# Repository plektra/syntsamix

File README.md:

# Syntsamix

A modular, analog stereo mixer for live electronic music: synthesizers, drum machines and Eurorack modular gear on one desk, with a resonant ladder filter on every channel and a compressor built for bass pumping.

> **Status: in design.** The specification is complete and the schematics for all four prototype boards are done. Nothing has been built yet: no PCB is laid out and the filter breadboard is still waiting for parts. Figures below are design targets, not measurements.

## Goals

- **Made for playing live.** Few controls, each with an obvious musical effect; the mixer is part of the performance, not only a utility.
- **Modular.** Identical stereo channel cards, added one at a time from 1 to 16. No card depends on another, and there is no backplane: cards are joined by multi-drop flat cables in 8-card sections, with the master card at one end.
- **Synth-friendly inputs.** Balanced inputs take everything from consumer line level to hot Eurorack signals of ±12 V peak, with no external attenuator.
- **Analog signal path** with pro headroom: +4 dBu nominal, about +20 dBu internal maximum, +24 dBu at the balanced outputs.
- **Cost-effective.** A tight budget: cheaper parts wherever the audible difference is small.
- **Open design** for anyone to build for themselves (non-commercial license, see below).

## Features

### Channel strip (stereo, every element an L/R pair)

- Balanced 6.3 mm TRS inputs (L/MONO and R) on a separate, swappable passive input module; a mono source in L/MONO feeds both sides
- One wide input trim (about -20 to +20 dB) with **soft clipping**, so overloads saturate gently
- Switchable 100 Hz low-cut
- **24 dB/octave ladder low-pass filter** (Sound Semiconductor SSI2144) with cutoff (20 Hz to 20 kHz), resonance and bypass. Driven "hot" for character, with resonance capped below self-oscillation and the bass loss half compensated
- Cutoff CV input at about 1 V/octave for modulation from modular gear
- 60 mm fader driving a VCA (SSI2162) with a console-style law: +10 dB at the top, 0 dB at 75 % of travel, fully off at the bottom; click-free mute
- Two stereo AUX sends (post-fader, jumper for pre-fader)
- Main or compressor bus assign
- **PFL** (pre-fader listen): headphones switch to the cue bus automatically while any PFL is on
- **SC send** to the sidechain bus and **DUCK**, which lets the channel duck with the sidechain trigger
- 8-segment LED level meter
- Lit latching buttons; stereo functions switch electronically, so buttons carry only logic

### Master and compressor

- **Performance compressor** on a dedicated compressor bus: Amount (threshold and makeup together), Release, Mix (parallel compression), click-free on/off and gain-reduction LEDs. Feed-forward log peak detector, about 1 ms attack, 4:1
- **Sidechain** from the compressor bus itself, the channels' sidechain bus or an external jack (audio or Eurorack gates and envelopes), with a 40 to 500 Hz low-pass so the kick drives the pumping. An SC listen button puts it in the headphones
- **Sidechain ducking**: an envelope follower (threshold, depth, decay) ducks any channel with DUCK on, independently of the compressor
- Two stereo AUX returns (level, mute, main or compressor bus; jumper for pro or pedal levels) and two AUX send masters
- Master level through a VCA, soft clipping on the master bus
- Balanced main outputs (TI DRV135, +24 dBu) and a headphone amplifier (TPA6120A2, 32 to 600 Ω)
- Stereo 12-segment master meter
- Output protection relays: silent power-up and power-down on the main and headphone outputs

### Construction

- Desktop unit: one PCB and a 35 mm FR4 top panel per channel strip, on an aluminium rail frame cut to length (about 650 to 700 mm wide at 16 strips)
- Powered by an off-the-shelf DC brick through a separate power board (24 V brick, non-isolated converters to ±20 V); every card regulates its own supply
- Separate audio and power ribbons, with audio and power grounds joined at a single star point
- RoHS compliant: every part needs a maker or supplier RoHS statement before it is chosen, and the boards are built lead-free

## Status

| Part | Schematic | PCB |
|---|---|---|
| Channel card | done (6 sheets, ERC clean; mechanical parts chosen) | waits for the filter breadboard |
| Master card | done (10 sheets, ERC clean) | not started |
| Input module (6.3 mm) | done | not started |
| Power board | done (4 sheets, ERC clean) | not started |

Also done: ngspice simulations of the filter gain structure, the compressor detector, the sidechain/ducking circuits and the fader level control (`simulation/`); the mechanical contract for strips, panels and frame ([`docs/MECHANICAL.md`](docs/MECHANICAL.md)); a RoHS audit of the parts register. Next: the SSI2144 breadboard, then PCB layout, starting with the channel card. The prototype has 4 channels.

The full roadmap and backlog (more input modules, direct outputs, 32 channels, and more) are in [`docs/ROADMAP.md`](docs/ROADMAP.md).

## Repository

| Path | Contents |
|---|---|
| [`docs/SPEC.md`](docs/SPEC.md) | Full specification and performance targets |
| [`docs/ARCHITECTURE.md`](docs/ARCHITECTURE.md) | System diagram, cross-board budgets and invariants |
| [`docs/decisions/`](docs/decisions/INDEX.md) | Every design decision, numbered and grouped by area |
| [`docs/CHAIN.md`](docs/CHAIN.md), [`docs/INPUT-MODULE.md`](docs/INPUT-MODULE.md) | Ribbon and input header pinouts |
| [`docs/MECHANICAL.md`](docs/MECHANICAL.md) | Strip envelope, panel stack, frame and card fixing |
| [`docs/parts.csv`](docs/parts.csv) | Parts register (`SX-` part numbers) |
| `hardware/` | KiCad projects: `channel-card`, `master`, `input-module-6p3`, `power`; shared libraries in `libs/` |
| `simulation/` | ngspice models, results and the breadboard plan |

Schematics are generated by Python scripts and checked pin by pin against an independent reference netlist; see `hardware/channel-card/scripts/README.md`. The design is developed with Claude Code; [`docs/WORKING-WITH-CLAUDE.md`](docs/WORKING-WITH-CLAUDE.md) describes the workflow.

## License

Source-available for **non-commercial** use; the author keeps all commercial rights. Hardware and documentation are CC BY-NC-SA 4.0, code is PolyForm Noncommercial 1.0.0. You may build, modify and play the mixer (paid gigs included), but not sell boards, kits or units without permission. Details in [`LICENSE.md`](LICENSE.md).

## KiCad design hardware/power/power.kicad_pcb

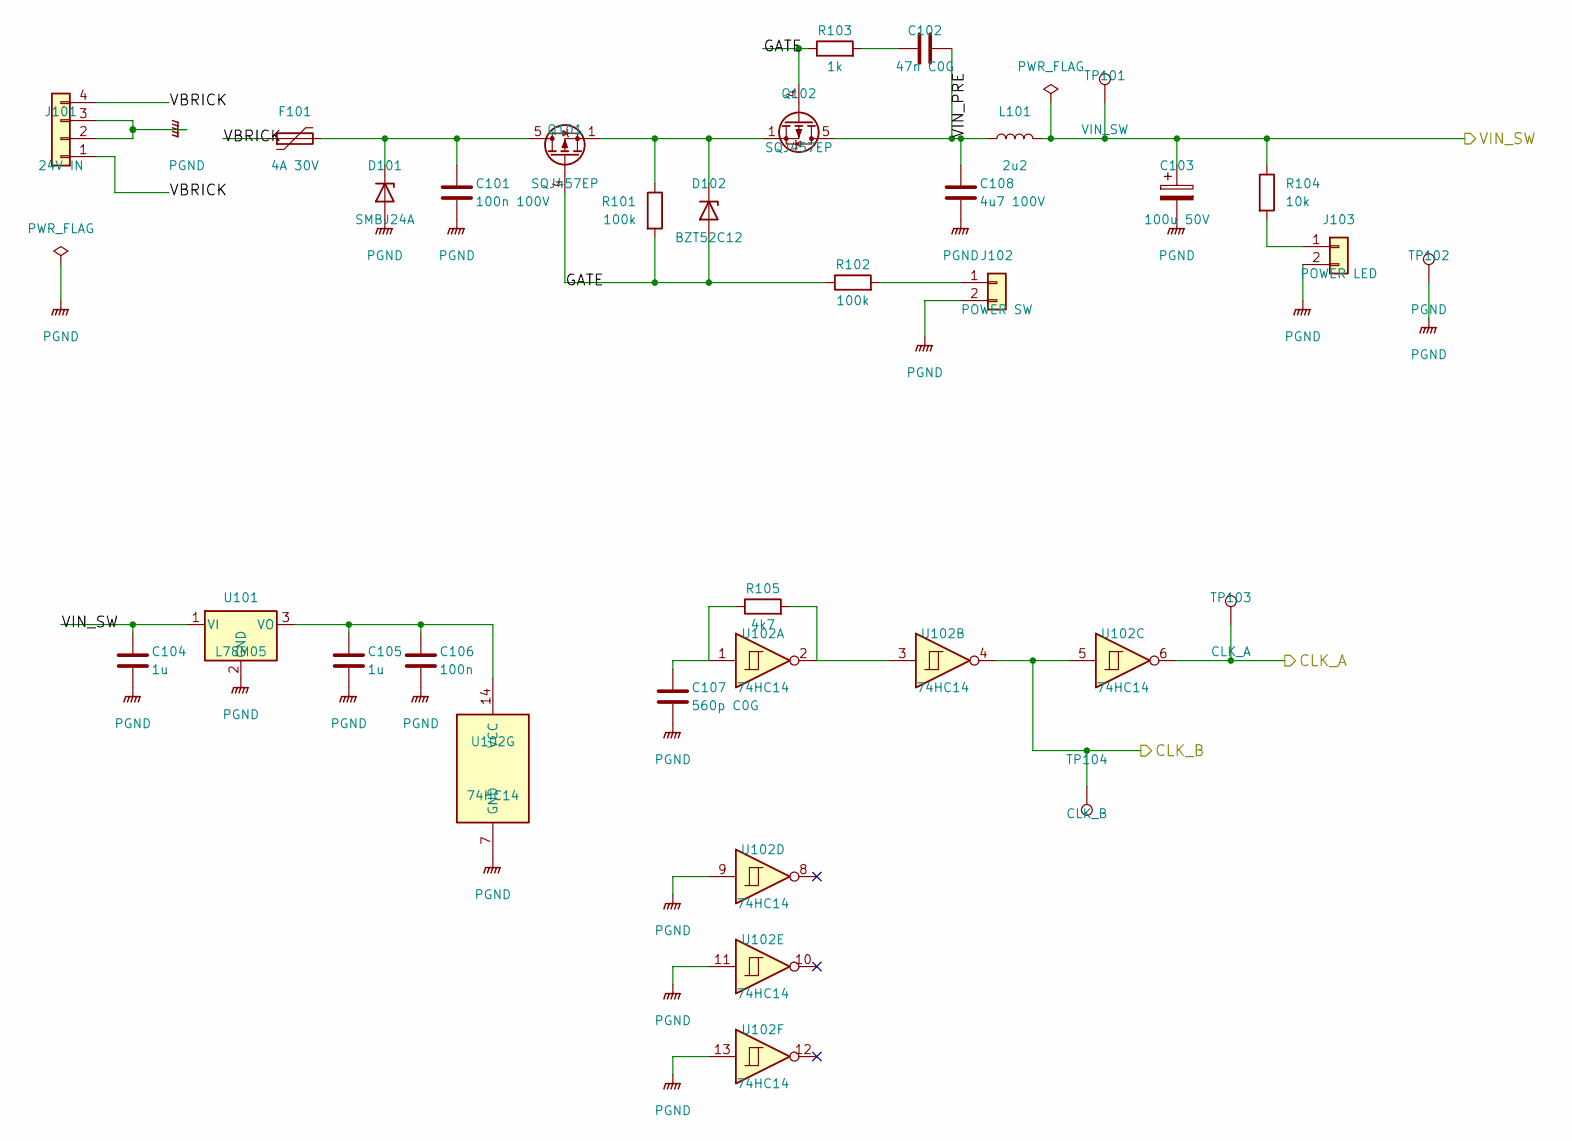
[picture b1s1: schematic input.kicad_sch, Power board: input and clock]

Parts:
C101: 100n 100V; C_0805_2012Metric
C102: 47n C0G; C_0805_2012Metric
C103: 100u 50V; CP_Radial_D8.0mm_P3.50mm; MPN UHE1H101MPD
C104, C105: 1u; C_0805_2012Metric
C106: 100n; C_0805_2012Metric
C107: 560p C0G; C_0805_2012Metric
C108: 4u7 100V; C_1210_3225Metric; MPN HMK325C7475KMHPE
D101: SMBJ24A; D_SMB; MPN SMBJ24A
D102: BZT52C12; D_SOD-123; MPN BZT52C12
F101: 4A 30V; Fuse_2920_7451Metric; MPN 2920L400/30GR
J101: 24V IN; JST_VH_B4P-VH_1x04_P3.96mm_Vertical; MPN B4P-VH(LF)(SN)
J102: POWER SW; JST_XH_B2B-XH-A_1x02_P2.50mm_Vertical; MPN B2B-XH-A(LF)(SN)
J103: POWER LED; JST_XH_B2B-XH-A_1x02_P2.50mm_Vertical; MPN B2B-XH-A(LF)(SN)
L101: 2u2; L_Bourns_SRP7028A_7.3x6.6mm; MPN SRP7028A-2R2M
Q101, Q102: SQJ457EP; PowerPAK_SO-8L_Single; MPN SQJ457EP-T1_GE3
R101, R102: 100k; R_0805_2012Metric
R103: 1k; R_0805_2012Metric
R104: 10k; R_0805_2012Metric
R105: 4k7; R_0805_2012Metric
TP101: VIN_SW; TestPoint_Pad_D1.5mm
TP102: PGND; TestPoint_Pad_D1.5mm
TP103: CLK_A; TestPoint_Pad_D1.5mm
TP104: CLK_B; TestPoint_Pad_D1.5mm
U101: L78M05; TO-252-2; MPN L78M05ABDT-TR
U102: 74HC14; SOIC-14_3.9x8.7mm_P1.27mm; MPN 74HC14D,653

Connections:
/CLK_A: TP103.1, U102.6; also elsewhere on the board
/CLK_B: TP104.1, U102.4, U102.5; also elsewhere on the board
/Input and clock/GATE: D102.2 (A), Q101.4 (G), Q102.4 (G), R101.2, R102.1, R103.1
/Input and clock/VBRICK: F101.1, J101.1, J101.4
/Input and clock/VIN_PRE: C102.2, C108.1, L101.1, Q102.5 (D)
unnamed: C102.1, R103.2
unnamed: C107.1, R105.1, U102.1
unnamed: C101.1, D101.1 (K), F101.2, Q101.5 (D)
unnamed: D102.1 (K), Q101.1 (S), Q101.2 (S), Q101.3 (S), Q102.1 (S), Q102.2 (S), Q102.3 (S), R101.1
unnamed: J102.1, R102.2
unnamed: J103.1, R104.2
unnamed: R105.2, U102.2, U102.3
unnamed: C105.1, C106.1, U101.3 (VO), U102.14 (VCC)

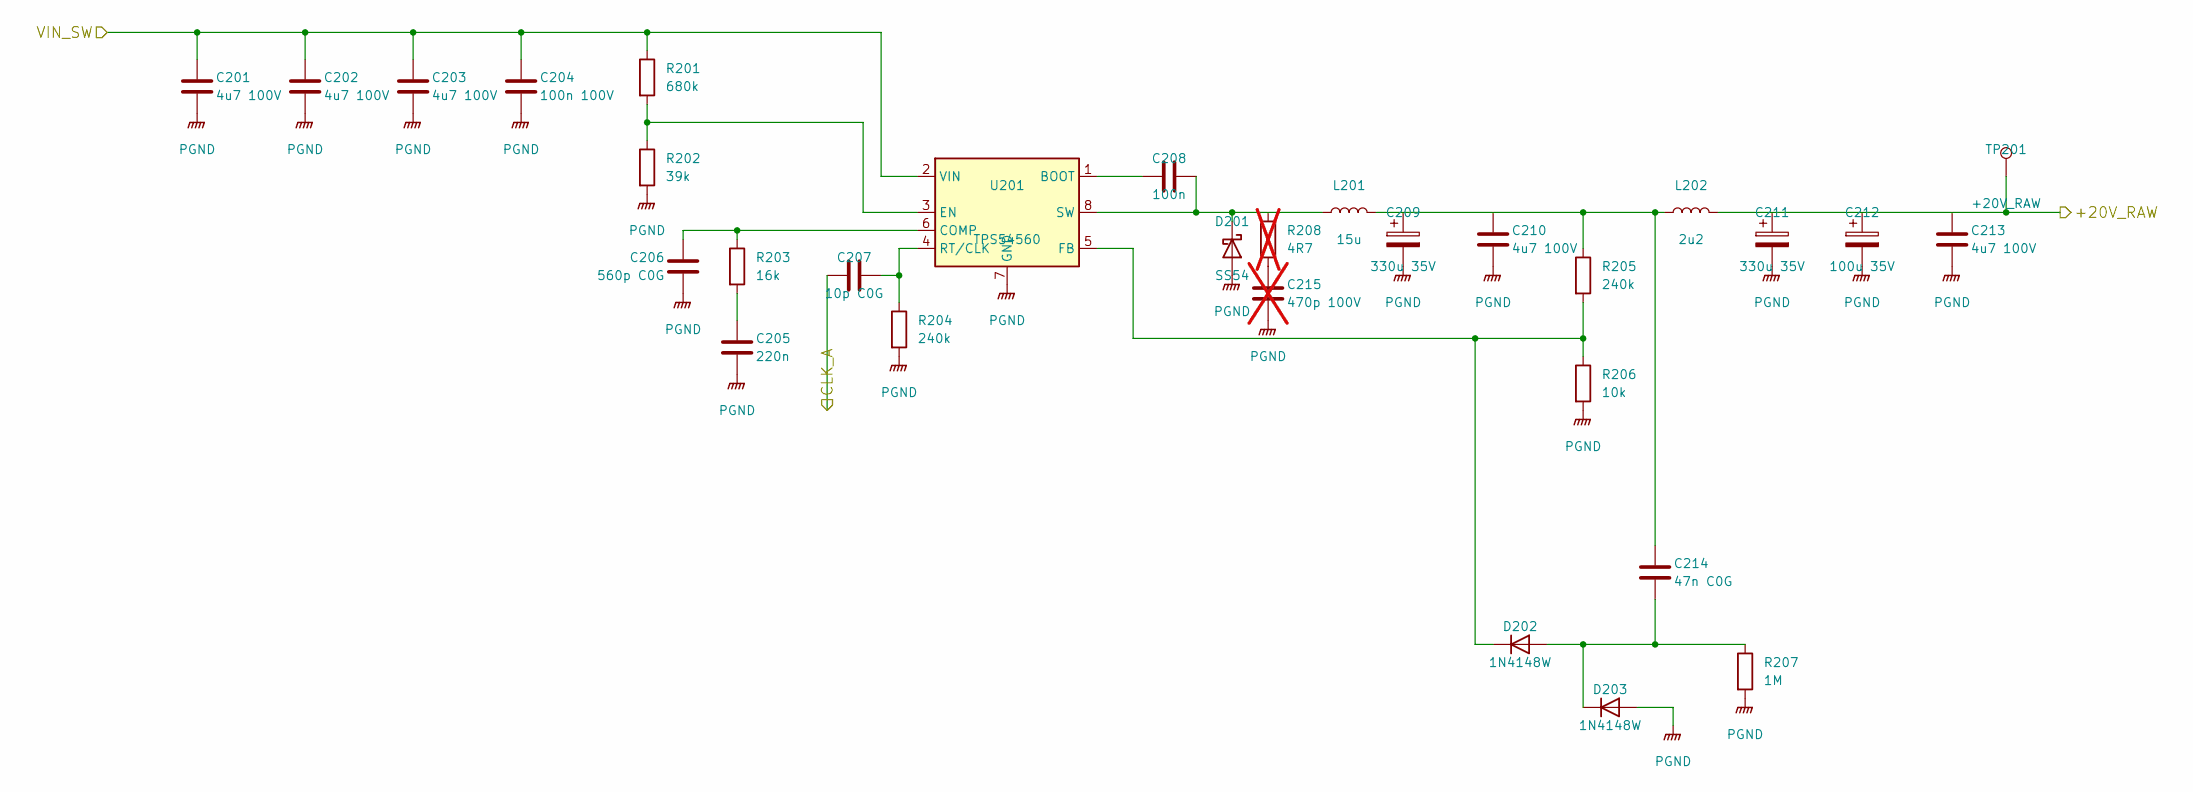
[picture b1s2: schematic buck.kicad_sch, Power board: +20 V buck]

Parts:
C201, C202, C203, C210, C213: 4u7 100V; C_1210_3225Metric; MPN HMK325C7475KMHPE
C204: 100n 100V; C_0805_2012Metric
C205: 220n; C_0805_2012Metric
C206: 560p C0G; C_0805_2012Metric
C207: 10p C0G; C_0603_1608Metric; MPN CL10C100JB8NNNC
C208: 100n; C_0805_2012Metric
C209, C211: 330u 35V; CP_Elec_10x10.5; MPN EEHZK1V331P
C212: 100u 35V; CP_Radial_D6.3mm_P2.50mm; MPN KNM2100UF35V149EC0055
C214: 47n C0G; C_0805_2012Metric
C215: 470p 100V; C_0805_2012Metric; not fitted
D201: SS54; D_SMA; MPN SS54
D202, D203: 1N4148W; D_SOD-123
L201: 15u; L_Bourns_SRP1265A; MPN SRP1265A-150M
L202: 2u2; L_Bourns_SRP7028A_7.3x6.6mm; MPN SRP7028A-2R2M
R201: 680k; R_0805_2012Metric; MPN 0805W8F6803T5E
R202: 39k; R_0805_2012Metric; MPN 0805W8F3902T5E
R203: 16k; R_0805_2012Metric; MPN 0805W8F1602T5E
R204, R205: 240k; R_0805_2012Metric
R206: 10k; R_0805_2012Metric
R207: 1M; R_0805_2012Metric
R208: 4R7; R_0805_2012Metric; not fitted
TP201: +20V_RAW; TestPoint_Pad_D1.5mm
U201: TPS54560; Texas_R-PDSO-G8_EP2.95x4.9mm_Mask2.4x3.1mm; MPN TPS54560DDAR

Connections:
/+20V_RAW: C211.1, C212.1, C213.1, L202.2, TP201.1; also elsewhere on the board
/CLK_A: C207.1; also elsewhere on the board
unnamed: C205.1, R203.2
unnamed: C209.1, C210.1, C214.1, L201.2, L202.1, R205.1
unnamed: C215.1, R208.2
unnamed: C208.2, D201.1 (K), L201.1, R208.1, U201.8 (SW)
unnamed: C214.2, D202.2 (A), D203.1 (K), R207.1
unnamed: D202.1 (K), R205.2, R206.1, U201.5 (FB)
unnamed: C208.1, U201.1 (BOOT)
unnamed: C206.1, R203.1, U201.6 (COMP)
unnamed: R201.2, R202.1, U201.3 (EN)
unnamed: C207.2, R204.1, U201.4 (RT/CLK)

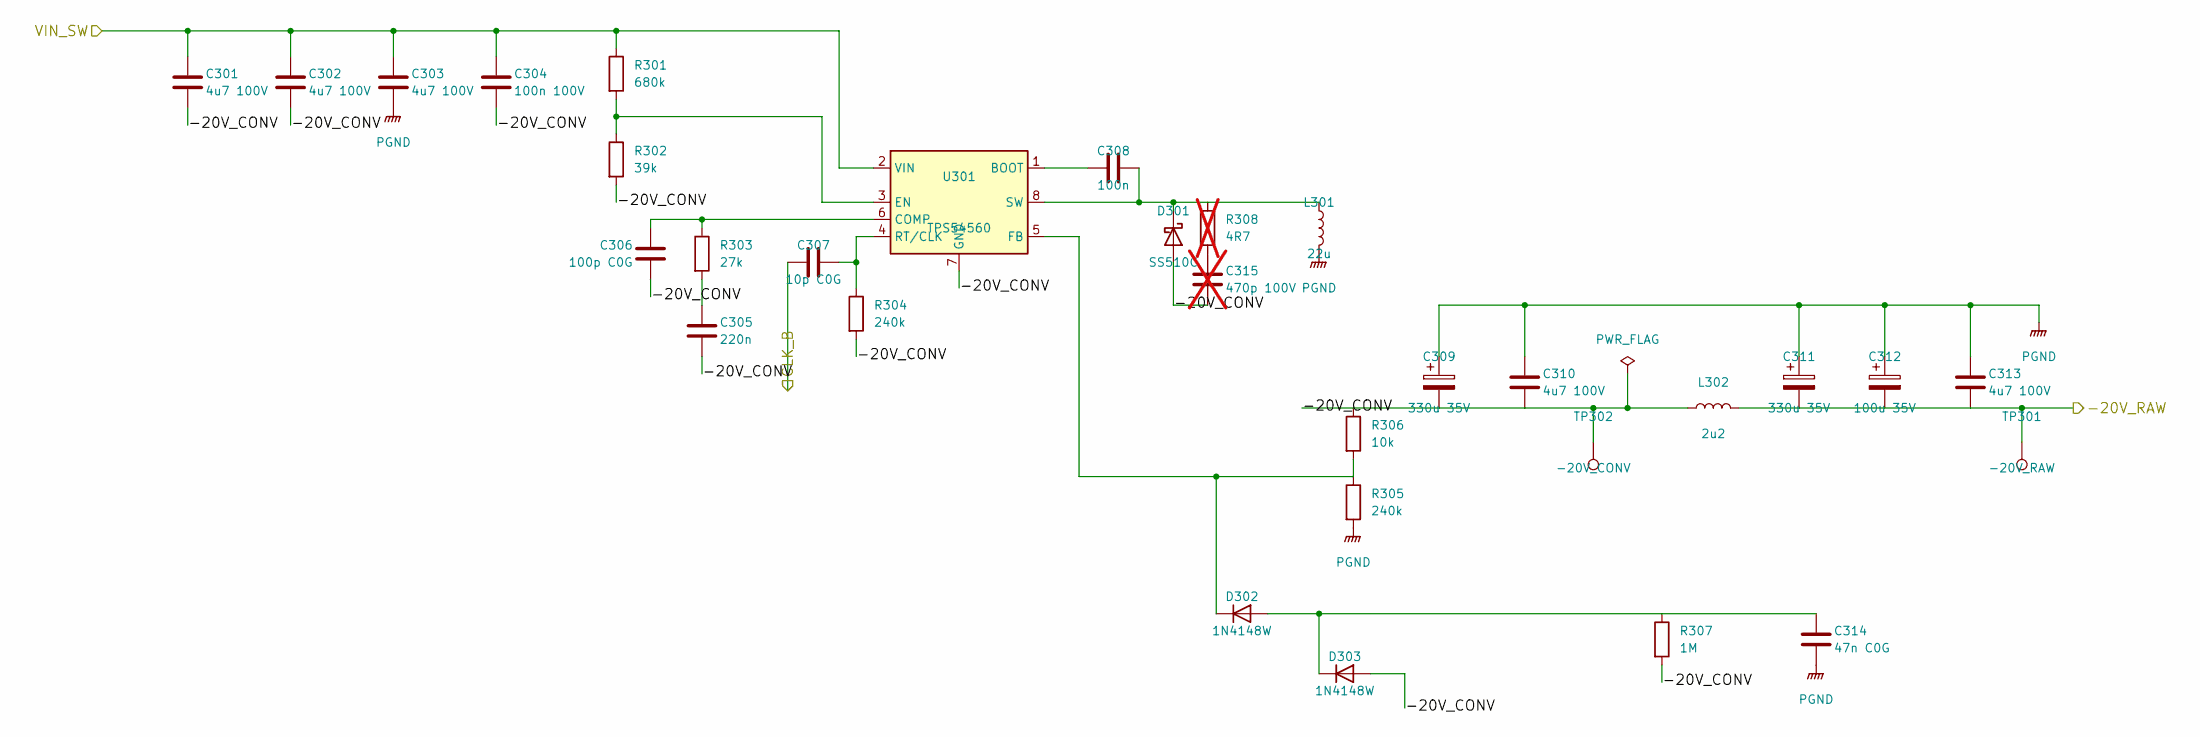
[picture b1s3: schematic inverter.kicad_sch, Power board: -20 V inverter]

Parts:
C301, C302, C303, C310, C313: 4u7 100V; C_1210_3225Metric; MPN HMK325C7475KMHPE
C304: 100n 100V; C_0805_2012Metric
C305: 220n; C_0805_2012Metric
C306: 100p C0G; C_0805_2012Metric
C307: 10p C0G; C_0603_1608Metric; MPN CL10C100JB8NNNC
C308: 100n; C_0805_2012Metric
C309, C311: 330u 35V; CP_Elec_10x10.5; MPN EEHZK1V331P
C312: 100u 35V; CP_Radial_D6.3mm_P2.50mm; MPN KNM2100UF35V149EC0055
C314: 47n C0G; C_0805_2012Metric
C315: 470p 100V; C_0805_2012Metric; not fitted
D301: SS510C; D_SMC; MPN SS510C
D302, D303: 1N4148W; D_SOD-123
L301: 22u; L_Bourns_SRP1265A; MPN SRP1265A-220M
L302: 2u2; L_Bourns_SRP7028A_7.3x6.6mm; MPN SRP7028A-2R2M
R301: 680k; R_0805_2012Metric; MPN 0805W8F6803T5E
R302: 39k; R_0805_2012Metric; MPN 0805W8F3902T5E
R303: 27k; R_0805_2012Metric
R304, R305: 240k; R_0805_2012Metric
R306: 10k; R_0805_2012Metric
R307: 1M; R_0805_2012Metric
R308: 4R7; R_0805_2012Metric; not fitted
TP301: -20V_RAW; TestPoint_Pad_D1.5mm
TP302: -20V_CONV; TestPoint_Pad_D1.5mm
U301: TPS54560; Texas_R-PDSO-G8_EP2.95x4.9mm_Mask2.4x3.1mm; MPN TPS54560DDAR

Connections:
/-20 V inverter/-20V_CONV: C301.2, C302.2, C304.2, C305.2, C306.2, C309.2, C310.2, C315.2, D301.2 (A), D303.2 (A), L302.1, R302.2, R304.2, R306.1, R307.2, TP302.1, U301.7 (GND), U301.9 (GND)
/-20V_RAW: C311.2, C312.2, C313.2, L302.2, TP301.1; also elsewhere on the board
/CLK_B: C307.1; also elsewhere on the board
unnamed: C305.1, R303.2
unnamed: C315.1, R308.2
unnamed: C308.2, D301.1 (K), L301.1, R308.1, U301.8 (SW)
unnamed: C314.1, D302.2 (A), D303.1 (K), R307.1
unnamed: D302.1 (K), R305.1, R306.2, U301.5 (FB)
unnamed: C308.1, U301.1 (BOOT)
unnamed: C306.1, R303.1, U301.6 (COMP)
unnamed: R301.2, R302.1, U301.3 (EN)
unnamed: C307.2, R304.1, U301.4 (RT/CLK)

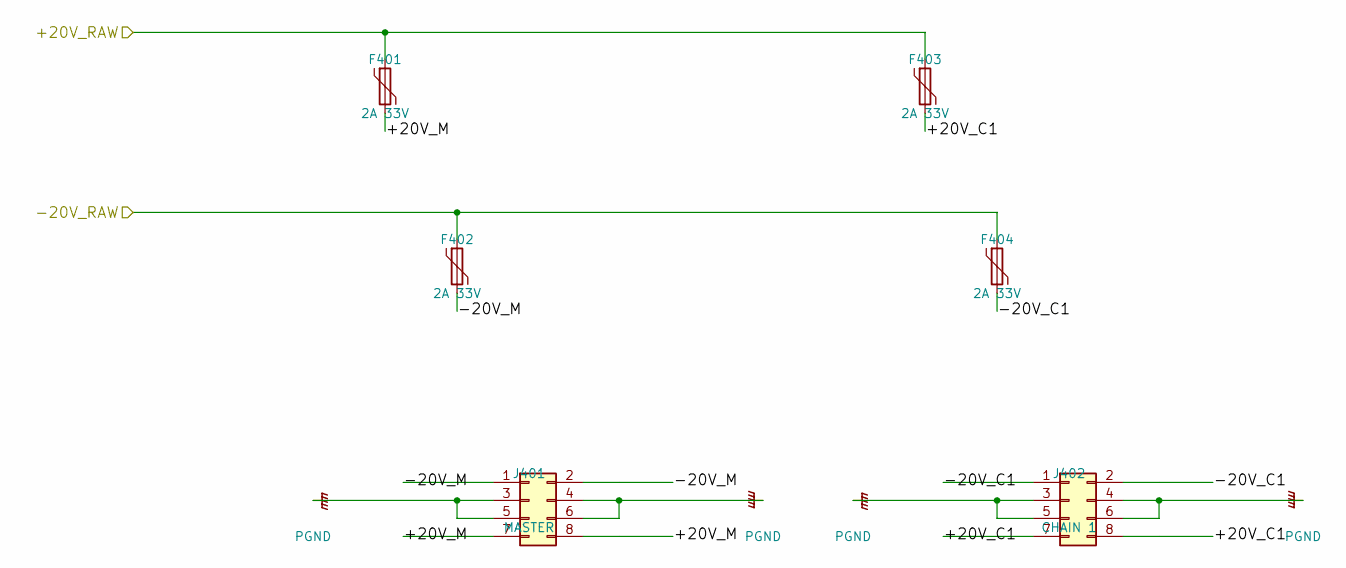
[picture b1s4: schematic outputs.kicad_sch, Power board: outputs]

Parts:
F401, F402, F403, F404: 2A 33V; Fuse_1812_4532Metric; MPN BSMD1812-200-33V
J401: MASTER; IDC-Header_2x04_P2.54mm_Vertical; MPN 61200821621
J402: CHAIN 1; IDC-Header_2x04_P2.54mm_Vertical; MPN 61200821621

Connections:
/+20V_RAW: F401.1, F403.1; also elsewhere on the board
/-20V_RAW: F402.1, F404.1; also elsewhere on the board
/Outputs/+20V_C1: F403.2, J402.7, J402.8
/Outputs/+20V_M: F401.2, J401.7, J401.8
/Outputs/-20V_C1: F404.2, J402.1, J402.2
/Outputs/-20V_M: F402.2, J401.1, J401.2

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
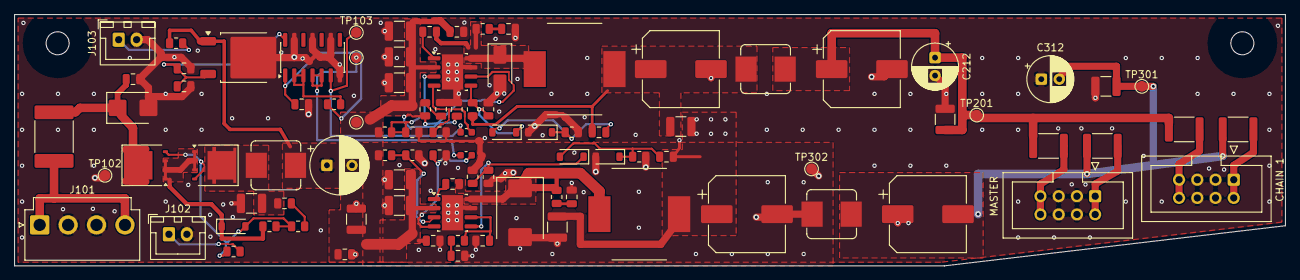
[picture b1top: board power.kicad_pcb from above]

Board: 2 copper layers, 177.0 x 35.0 mm, 97 parts (0 on the bottom side), 41 nets.

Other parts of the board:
H1, H2: bracket M3; MountingHole_3.2mm_M3
